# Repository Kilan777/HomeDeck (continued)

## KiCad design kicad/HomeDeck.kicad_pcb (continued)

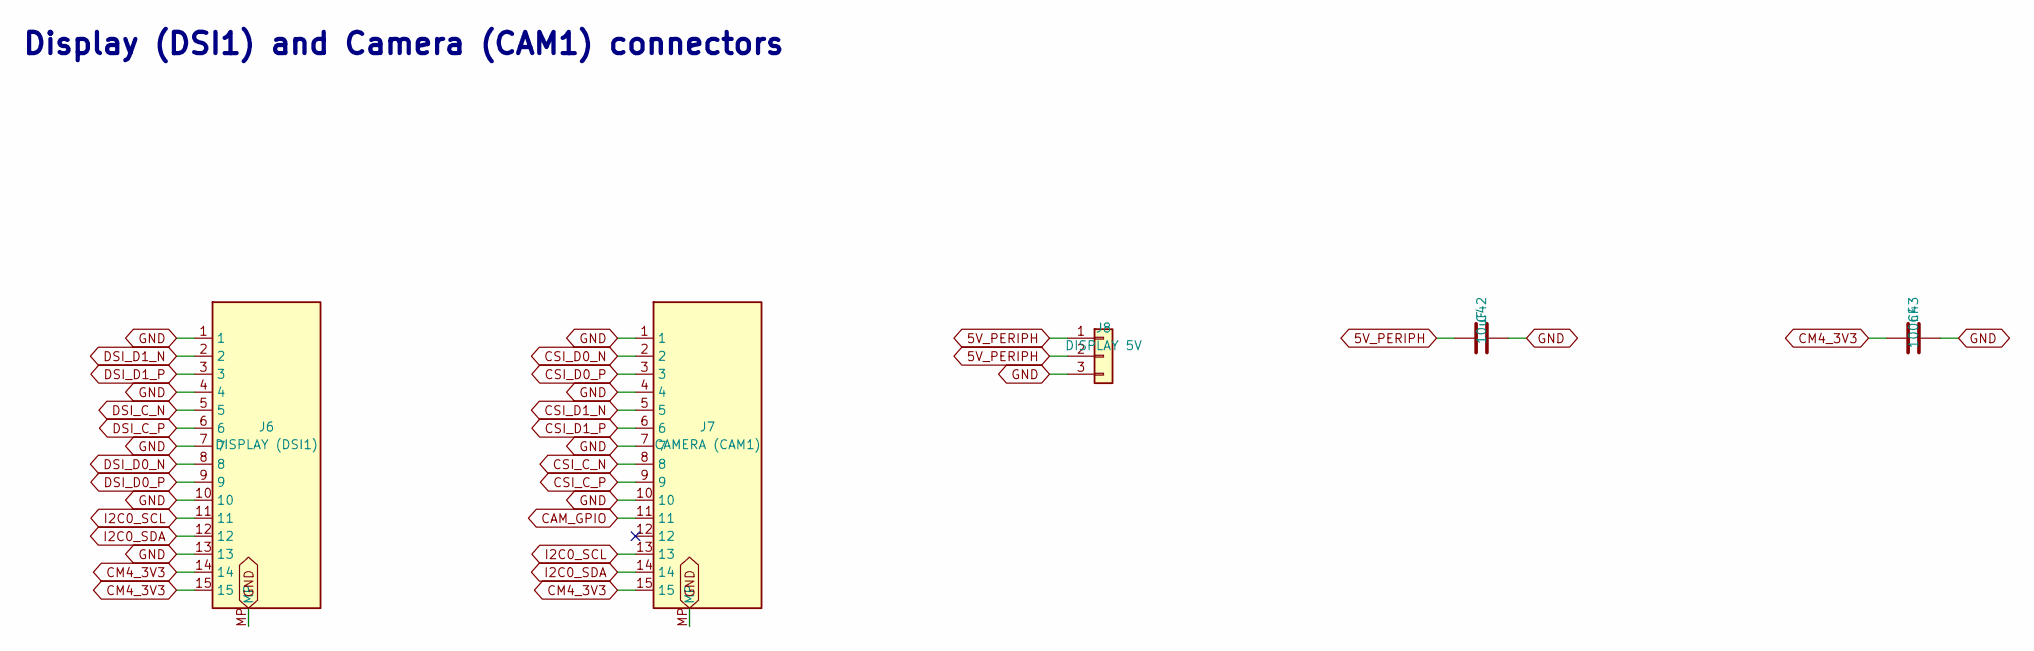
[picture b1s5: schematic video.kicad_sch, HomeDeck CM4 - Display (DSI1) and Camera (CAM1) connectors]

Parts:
C42: 10uF; C_0603_1608Metric; LCSC C96446
C43: 100nF; C_0603_1608Metric; LCSC C14663
J6: DISPLAY (DSI1); FPC_15P_1.0mm_BottomContact_RA; MPN 1.0-15PContact,Bottom; LCSC C66660
J7: CAMERA (CAM1); FPC_15P_1.0mm_BottomContact_RA; MPN 1.0-15PContact,Bottom; LCSC C66660
J8: DISPLAY 5V; PinHeader_1x03_P2.54mm_Vertical; MPN B-2100S03P-A110; LCSC C124376

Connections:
5V_PERIPH: C42.1, J8.1, J8.2; also elsewhere on the board
CAM_GPIO: J7.11; also elsewhere on the board
CM4_3V3: C43.1, J6.14, J6.15, J7.15; also elsewhere on the board
CSI_C_N: J7.8; also elsewhere on the board
CSI_C_P: J7.9; also elsewhere on the board
CSI_D0_N: J7.2; also elsewhere on the board
CSI_D0_P: J7.3; also elsewhere on the board
CSI_D1_N: J7.5; also elsewhere on the board
CSI_D1_P: J7.6; also elsewhere on the board
DSI_C_N: J6.5; also elsewhere on the board
DSI_C_P: J6.6; also elsewhere on the board
DSI_D0_N: J6.8; also elsewhere on the board
DSI_D0_P: J6.9; also elsewhere on the board
DSI_D1_N: J6.2; also elsewhere on the board
DSI_D1_P: J6.3; also elsewhere on the board
GND: C42.2, C43.2, J6.1, J6.4, J6.7, J6.10, J6.13, J6.MP, J7.1, J7.4, J7.7, J7.10, J7.MP, J8.3; also elsewhere on the board
I2C0_SCL: J6.11, J7.13; also elsewhere on the board
I2C0_SDA: J6.12, J7.14; also elsewhere on the board

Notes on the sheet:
Display (DSI1) and Camera (CAM1) connectors

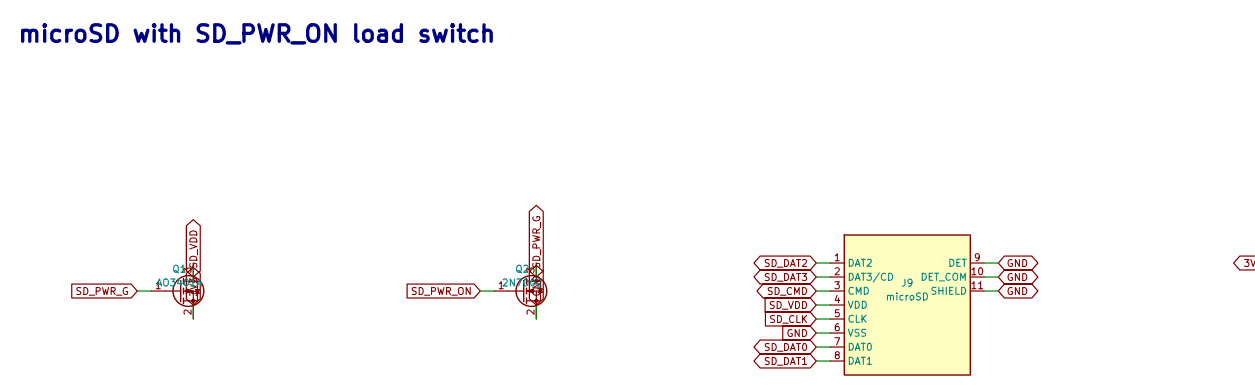
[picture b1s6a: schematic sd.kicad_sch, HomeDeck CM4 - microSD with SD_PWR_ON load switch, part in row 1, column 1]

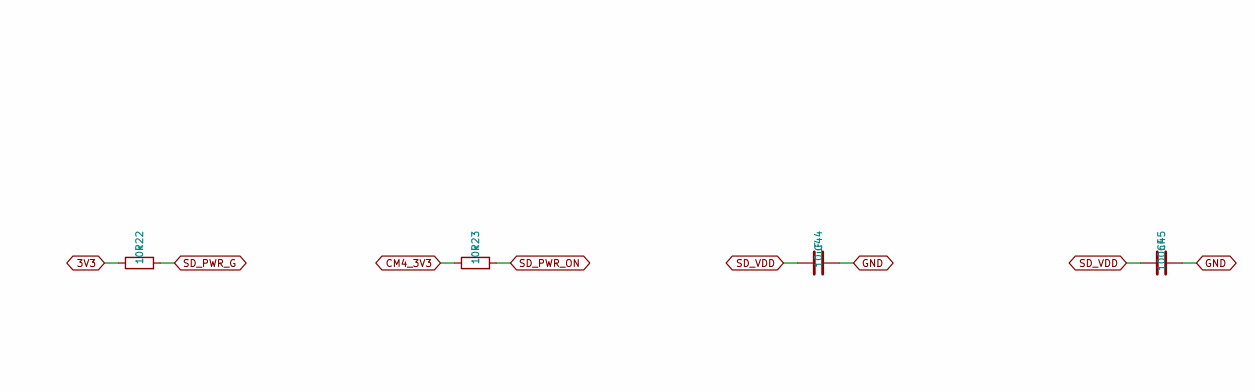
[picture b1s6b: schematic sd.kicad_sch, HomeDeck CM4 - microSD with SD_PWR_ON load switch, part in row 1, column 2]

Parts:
C44: 10uF; C_0603_1608Metric; LCSC C96446
C45: 100nF; C_0603_1608Metric; LCSC C14663
J9: microSD; microSD_HC_Molex_104031-0811; MPN 104031-0811; LCSC C585350
Q1: AO3401A; SOT-23; MPN AO3401A; LCSC C15127
Q2: 2N7002; SOT-23; MPN 2N7002; LCSC C8545
R22, R23: 10k; R_0603_1608Metric; LCSC C25804

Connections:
3V3: Q1.2 (S), R22.1; also elsewhere on the board
CM4_3V3: R23.1; also elsewhere on the board
GND: C44.2, C45.2, J9.6 (VSS), J9.9 (DET), J9.10 (DET_COM), J9.11 (SHIELD), Q2.2 (S); also elsewhere on the board
SD_CLK: J9.5 (CLK); also elsewhere on the board
SD_CMD: J9.3 (CMD); also elsewhere on the board
SD_DAT0: J9.7 (DAT0); also elsewhere on the board
SD_DAT1: J9.8 (DAT1); also elsewhere on the board
SD_DAT2: J9.1 (DAT2); also elsewhere on the board
SD_DAT3: J9.2 (DAT3/CD); also elsewhere on the board
SD_PWR_G: Q1.1 (G), Q2.3 (D), R22.2
SD_PWR_ON: Q2.1 (G), R23.2; also elsewhere on the board
SD_VDD: C44.1, C45.1, J9.4 (VDD), Q1.3 (D)

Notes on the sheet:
microSD with SD_PWR_ON load switch

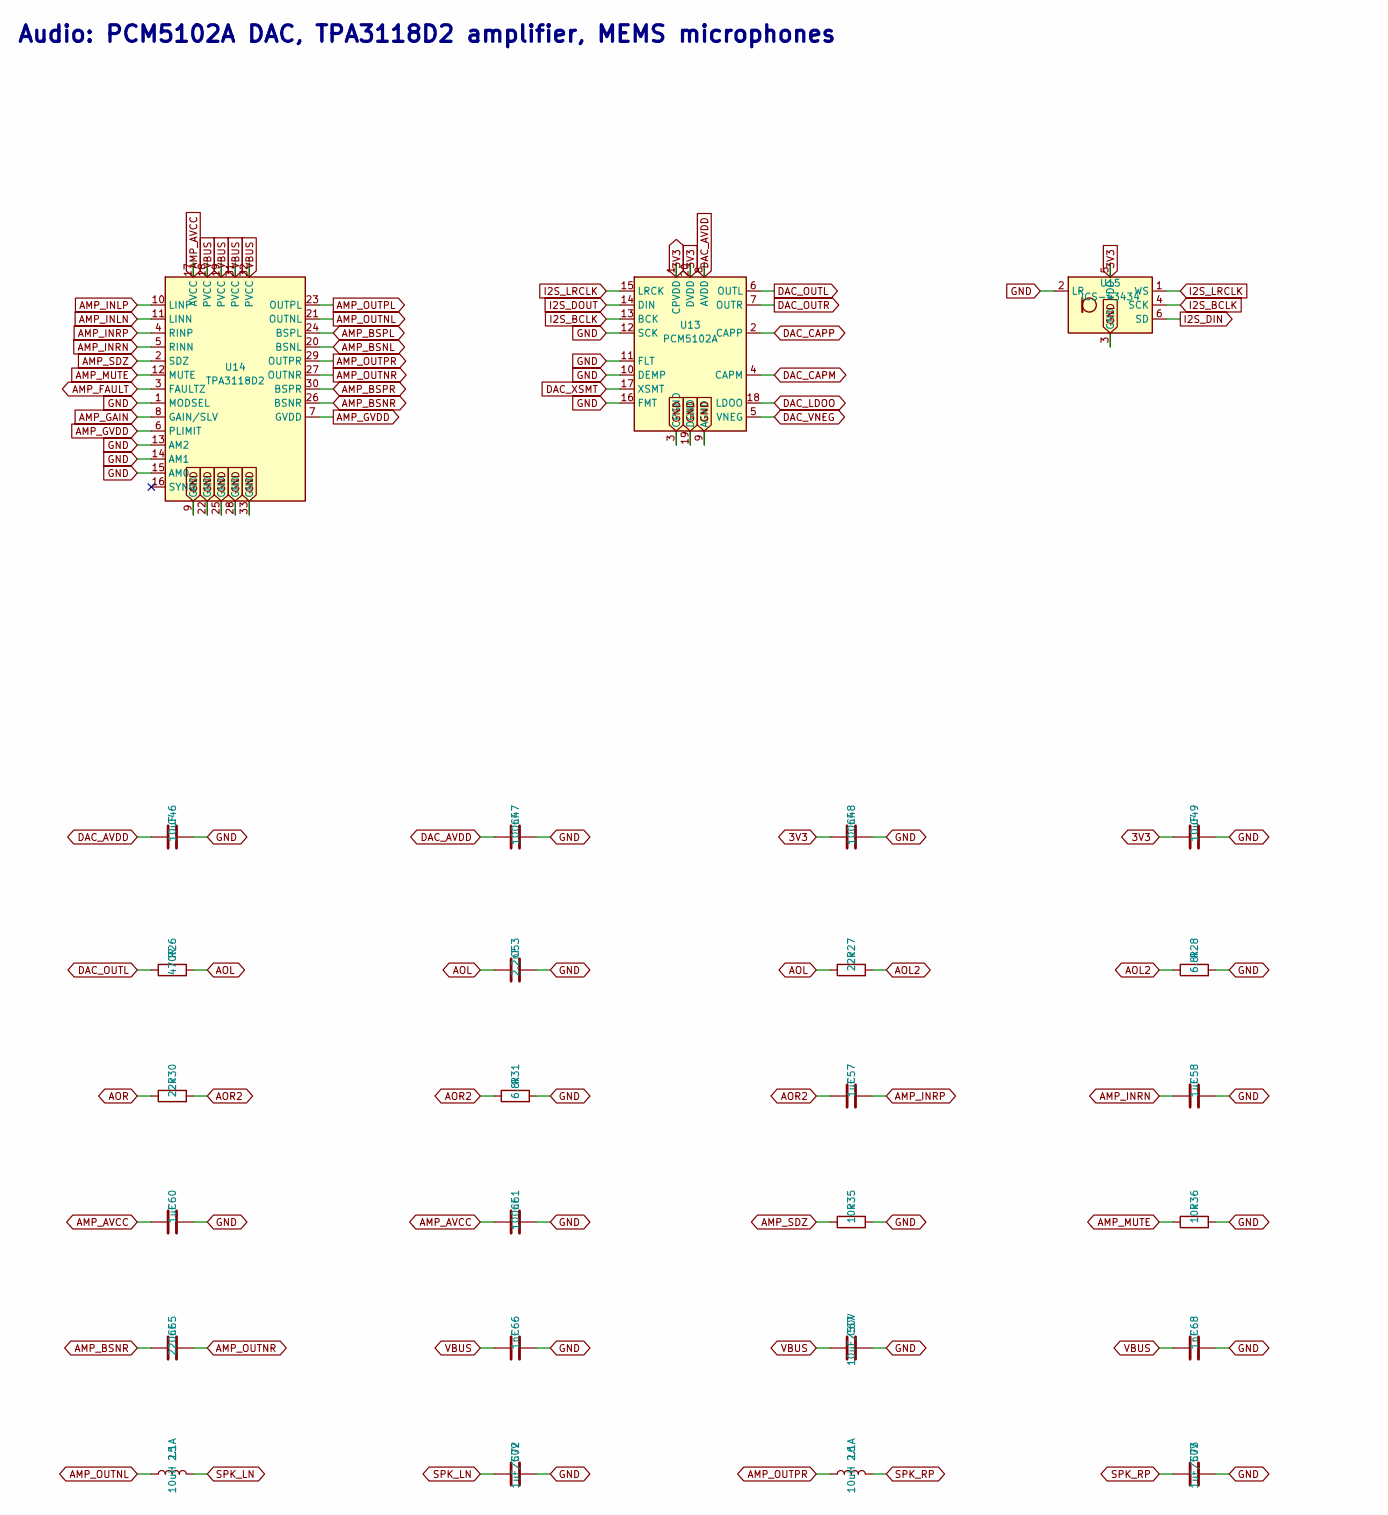
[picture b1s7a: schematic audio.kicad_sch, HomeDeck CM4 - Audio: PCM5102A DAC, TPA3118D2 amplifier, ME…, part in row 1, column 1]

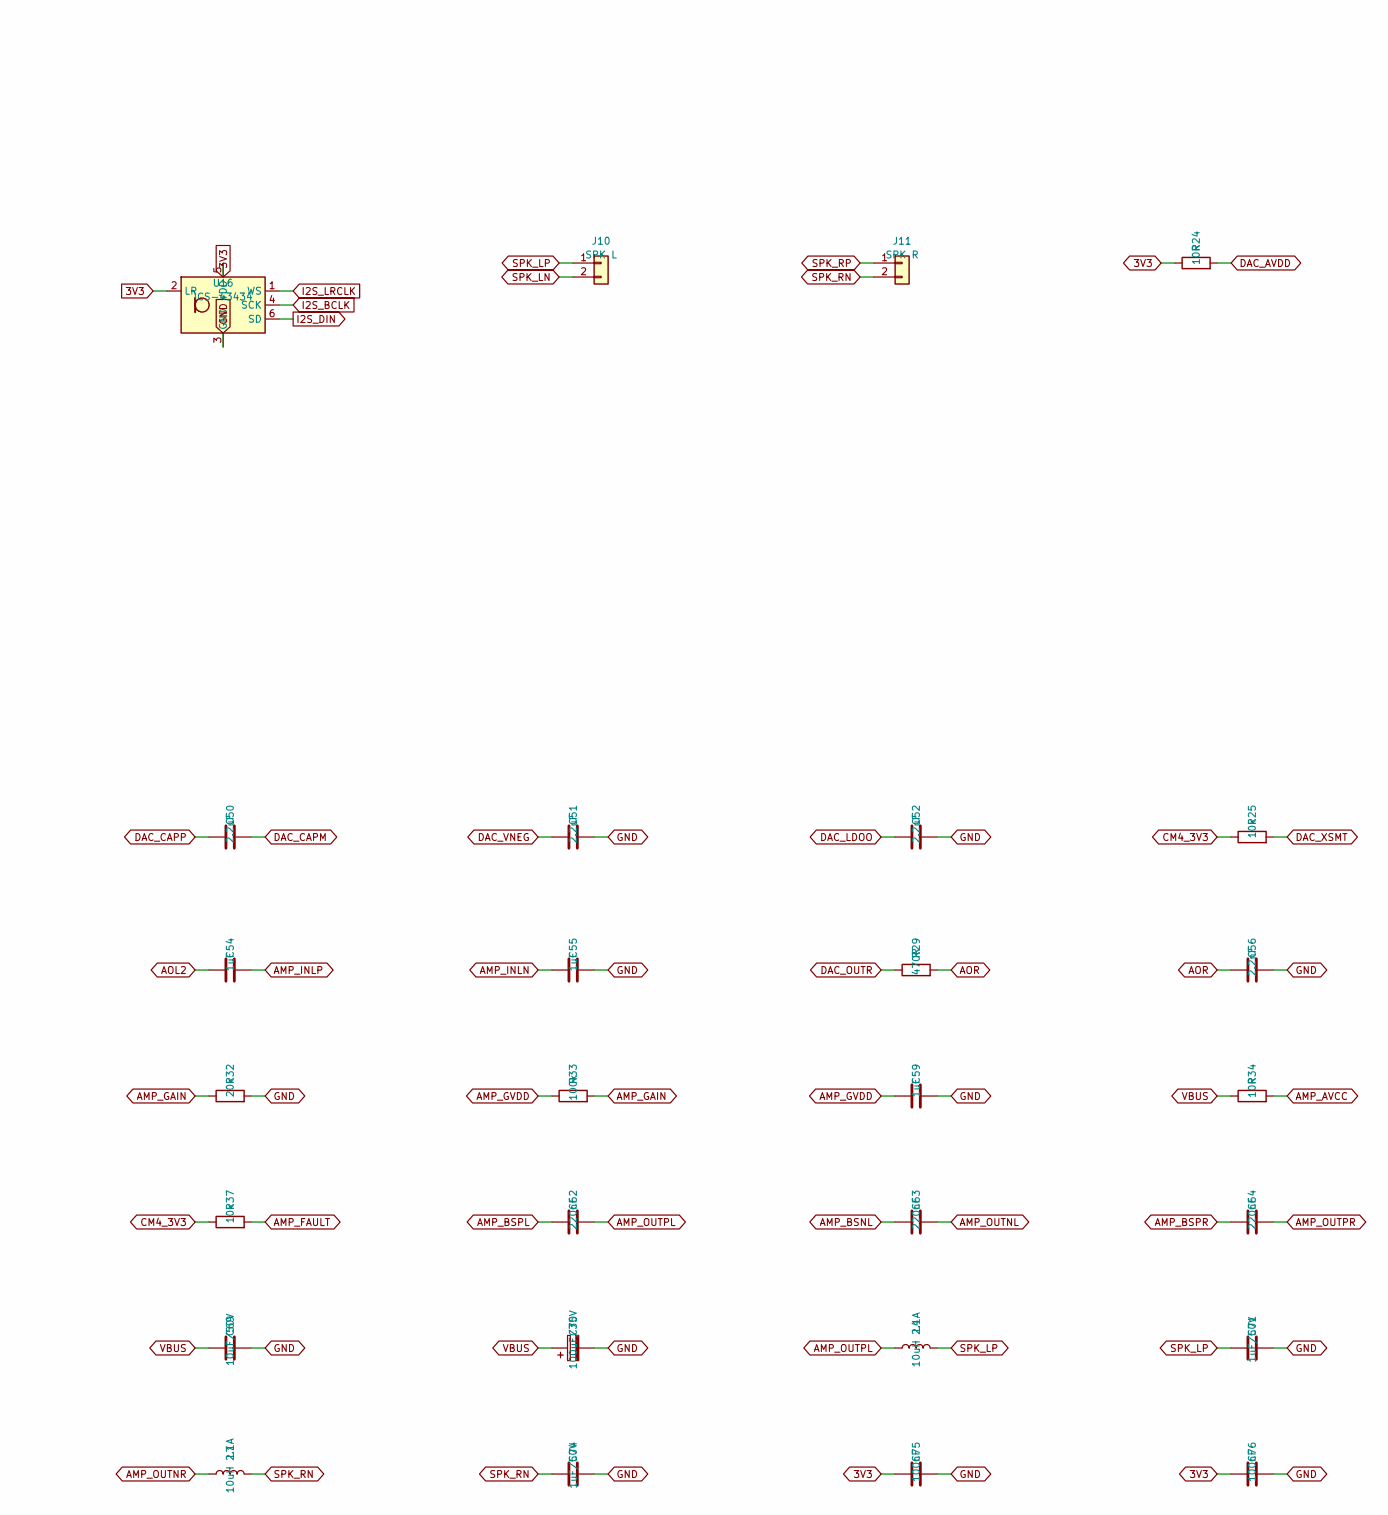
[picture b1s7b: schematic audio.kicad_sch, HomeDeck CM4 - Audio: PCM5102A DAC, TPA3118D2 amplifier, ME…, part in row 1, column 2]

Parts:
C46, C49: 10uF; C_0603_1608Metric; LCSC C96446
C47, C48, C61, C75, C76: 100nF; C_0603_1608Metric; LCSC C14663
C50, C51, C52: 2.2uF; C_0603_1608Metric; LCSC C23630
C53, C56: 2.2nF; C_0603_1608Metric; LCSC C1604
C54, C55, C57, C58, C59, C60: 1uF; C_0603_1608Metric; LCSC C15849
C62, C63, C64, C65: 220nF; C_0603_1608Metric; LCSC C21120
C66, C68: 1nF; C_0603_1608Metric; LCSC C1588
C67, C69: 10uF/50V; C_1206_3216Metric; LCSC C13585
C70: 100uF/35V; CP_Elec_6.3x7.7; LCSC C3339
C71, C72, C73, C74: 1uF/50V; C_0805_2012Metric; LCSC C28323
J10: SPK L; JST_PH_S2B-PH-K_1x02_P2.00mm_Horizontal; MPN S2B-PH-K-S; LCSC C173752
J11: SPK R; JST_PH_S2B-PH-K_1x02_P2.00mm_Horizontal; MPN S2B-PH-K-S; LCSC C173752
L4, L5, L6, L7: 10uH 2.1A; L_Sunlord_SWPA5040S; MPN SWPA5040S100MT; LCSC C84608
R24, R34: 10R; R_0603_1608Metric; LCSC C22859
R25, R35, R36, R37: 10k; R_0603_1608Metric; LCSC C25804
R26, R29: 470R; R_0603_1608Metric; LCSC C23179
R27, R30: 22k; R_0603_1608Metric; LCSC C31850
R28, R31: 6.8k; R_0603_1608Metric; LCSC C23212
R32: 20k; R_0603_1608Metric; LCSC C4184
R33: 100k; R_0603_1608Metric; LCSC C25803
U13: PCM5102A; TSSOP-20_4.4x6.5mm_P0.65mm; MPN PCM5102APWR; LCSC C107671
U14: TPA3118D2; HTSSOP-32-1EP_6.1x11mm_P0.65mm_EP5.2x11mm_Mask4.11x4.36mm_T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; MPN TPA3118D2DAPR; LCSC C46497
U15, U16: ICS-43434; InvenSense_ICS-43434-6_3.5x2.65mm; MPN ICS-43434; LCSC C5656610

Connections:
3V3: C48.1, C49.1, C75.1, C76.1, R24.1, U13.1 (CPVDD), U13.20 (DVDD), U15.5 (VDD), U16.2 (LR), U16.5 (VDD); also elsewhere on the board
AMP_AVCC: C60.1, C61.1, R34.2, U14.17 (AVCC)
AMP_BSNL: C63.1, U14.20 (BSNL)
AMP_BSNR: C65.1, U14.26 (BSNR)
AMP_BSPL: C62.1, U14.24 (BSPL)
AMP_BSPR: C64.1, U14.30 (BSPR)
AMP_FAULT: R37.2, U14.3 (FAULTZ); also elsewhere on the board
AMP_GAIN: R32.1, R33.2, U14.8 (GAIN/SLV)
AMP_GVDD: C59.1, R33.1, U14.6 (PLIMIT), U14.7 (GVDD)
AMP_INLN: C55.1, U14.11 (LINN)
AMP_INLP: C54.2, U14.10 (LINP)
AMP_INRN: C58.1, U14.5 (RINN)
AMP_INRP: C57.2, U14.4 (RINP)
AMP_MUTE: R36.1, U14.12 (MUTE); also elsewhere on the board
AMP_OUTNL: C63.2, L5.1, U14.21 (OUTNL)
AMP_OUTNR: C65.2, L7.1, U14.27 (OUTNR)
AMP_OUTPL: C62.2, L4.1, U14.23 (OUTPL)
AMP_OUTPR: C64.2, L6.1, U14.29 (OUTPR)
AMP_SDZ: R35.1, U14.2 (SDZ); also elsewhere on the board
AOL: C53.1, R26.2, R27.1
AOL2: C54.1, R27.2, R28.1
AOR: C56.1, R29.2, R30.1
AOR2: C57.1, R30.2, R31.1
CM4_3V3: R25.1, R37.1; also elsewhere on the board
DAC_AVDD: C46.1, C47.1, R24.2, U13.8 (AVDD)
DAC_CAPM: C50.2, U13.4 (CAPM)
DAC_CAPP: C50.1, U13.2 (CAPP)
DAC_LDOO: C52.1, U13.18 (LDOO)
DAC_OUTL: R26.1, U13.6 (OUTL)
DAC_OUTR: R29.1, U13.7 (OUTR)
DAC_VNEG: C51.1, U13.5 (VNEG)
DAC_XSMT: R25.2, U13.17 (XSMT); also elsewhere on the board
GND: C46.2, C47.2, C48.2, C49.2, C51.2, C52.2, C53.2, C55.2, C56.2, C58.2, C59.2, C60.2, C61.2, C66.2, C67.2, C68.2, C69.2, C70.2, C71.2, C72.2, C73.2, C74.2, C75.2, C76.2, R28.2, R31.2, R32.2, R35.2, R36.2, U13.3 (CPGND), U13.9 (AGND), U13.10 (DEMP), U13.11 (FLT), U13.12 (SCK), U13.16 (FMT), U13.19 (DGND), U14.1 (MODSEL), U14.9 (GND), U14.13 (AM2), U14.14 (AM1), U14.15 (AM0), U14.22 (GND), U14.25 (GND), U14.28 (GND), U14.33 (GND), U15.2 (LR), U15.3 (GND), U16.3 (GND); also elsewhere on the board
I2S_BCLK: U13.13 (BCK), U15.4 (SCK), U16.4 (SCK); also elsewhere on the board
I2S_DIN: U15.6 (SD), U16.6 (SD); also elsewhere on the board
I2S_DOUT: U13.14 (DIN); also elsewhere on the board
I2S_LRCLK: U13.15 (LRCK), U15.1 (WS), U16.1 (WS); also elsewhere on the board
SPK_LN: C72.1, J10.2, L5.2
SPK_LP: C71.1, J10.1, L4.2
SPK_RN: C74.1, J11.2, L7.2
SPK_RP: C73.1, J11.1, L6.2
VBUS: C66.1, C67.1, C68.1, C69.1, C70.1, R34.1, U14.18 (PVCC), U14.19 (PVCC), U14.31 (PVCC), U14.32 (PVCC); also elsewhere on the board

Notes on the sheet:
Audio: PCM5102A DAC, TPA3118D2 amplifier, MEMS microphones

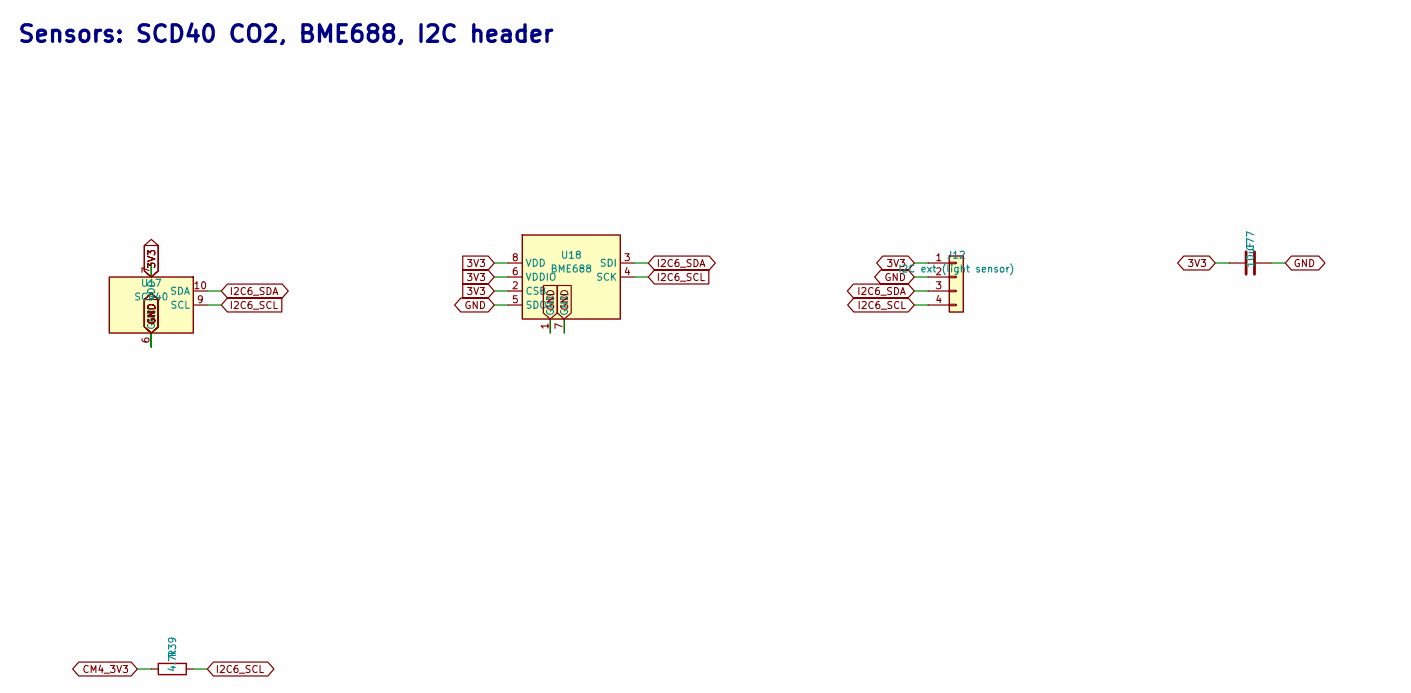
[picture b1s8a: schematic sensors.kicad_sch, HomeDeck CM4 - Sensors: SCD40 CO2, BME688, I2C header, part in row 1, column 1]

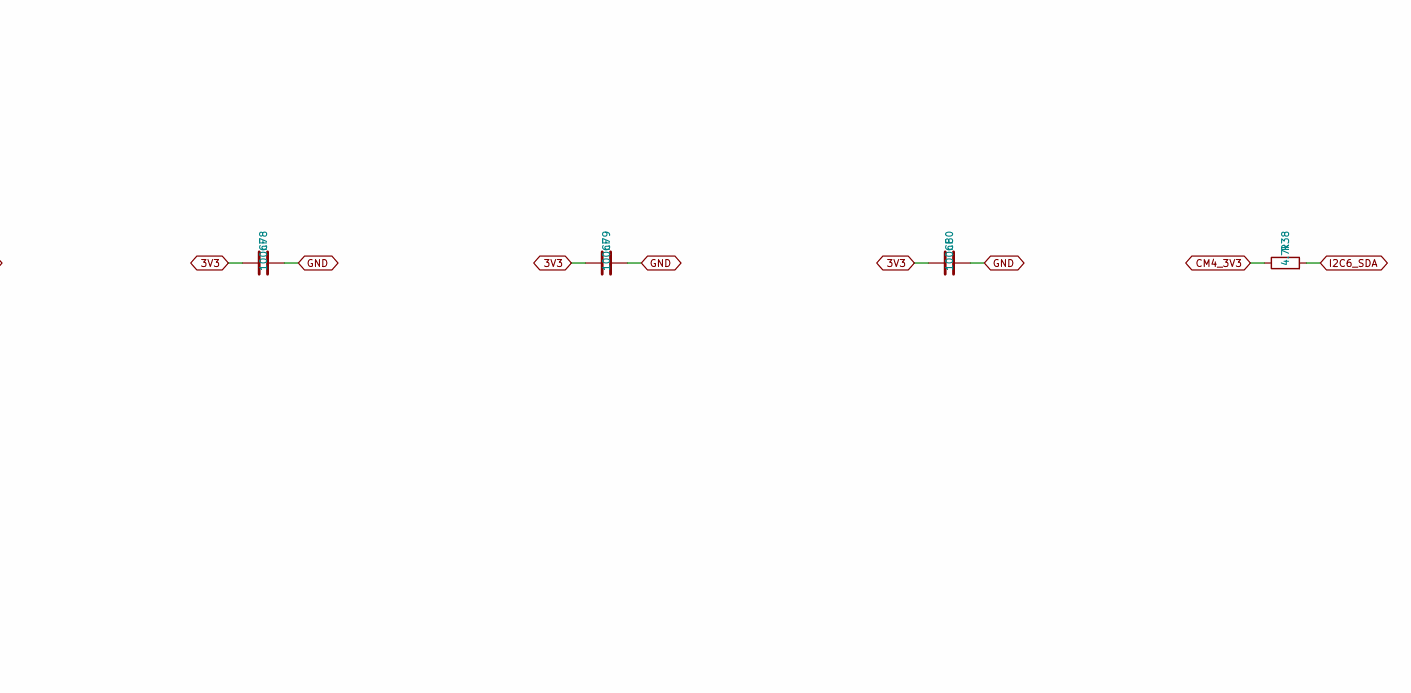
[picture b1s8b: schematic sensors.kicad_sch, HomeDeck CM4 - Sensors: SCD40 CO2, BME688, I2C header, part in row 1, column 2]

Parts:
C77: 10uF; C_0603_1608Metric; LCSC C96446
C78, C79, C80: 100nF; C_0603_1608Metric; LCSC C14663
J12: I2C ext (light sensor); PinHeader_1x04_P2.54mm_Vertical; MPN B-2100S04P-A110; LCSC C124378
R38, R39: 4.7k; R_0603_1608Metric; LCSC C23162
U17: SCD40; Sensirion_SCD4x-1EP_10.1x10.1mm_P1.25mm_EP4.8x4.8mm; MPN SCD40-D-R2; LCSC C3659421
U18: BME688; Bosch_LGA-8_3x3mm_P0.8mm_ClockwisePinNumbering; MPN BME688; LCSC C3664478

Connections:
3V3: C77.1, C78.1, C79.1, C80.1, J12.1, U17.7 (VDD), U17.19 (VDD), U18.2 (CSB), U18.6 (VDDIO), U18.8 (VDD); also elsewhere on the board
CM4_3V3: R38.1, R39.1; also elsewhere on the board
GND: C77.2, C78.2, C79.2, C80.2, J12.2, U17.6 (GND), U17.20 (GND), U17.21 (GND), U18.1 (GND), U18.5 (SDO), U18.7 (GND); also elsewhere on the board
I2C6_SCL: J12.4, R39.2, U17.9 (SCL), U18.4 (SCK); also elsewhere on the board
I2C6_SDA: J12.3, R38.2, U17.10 (SDA), U18.3 (SDI); also elsewhere on the board

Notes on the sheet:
Sensors: SCD40 CO2, BME688, I2C header

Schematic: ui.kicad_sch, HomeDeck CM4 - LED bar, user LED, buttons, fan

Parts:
C81, C82, C83, C84, C85, C86, C87, C88, C89, C90, C91, C93, C94, C95: 100nF; C_0603_1608Metric; LCSC C14663
C92: 10uF; C_0603_1608Metric; LCSC C96446
D5: USER (green); LED_0805_2012Metric; MPN KT-0805G; LCSC C2297
D6: SS34; D_SMA; MPN SS34; LCSC C8678
D10, D11, D12, D13, D14, D15, D16, D17, D18, D19: WS2812B; LED_WS2812B_PLCC4_5.0x5.0mm_P3.2mm; MPN WS2812B-B/T; LCSC C2761795
J17: LED strip ext; JST_PH_S3B-PH-K_1x03_P2.00mm_Horizontal; MPN S3B-PH-K-S; LCSC C157929
J18, J19, J20: ext button; PinHeader_1x02_P2.54mm_Vertical; MPN B-2100S02P-A110; LCSC C124375
J21: FAN 5V; JST_PH_S2B-PH-K_1x02_P2.00mm_Horizontal; MPN S2B-PH-K-S; LCSC C173752
Q3: AO3400A; SOT-23; MPN AO3400A; LCSC C20917
R40: 330R; R_0603_1608Metric; LCSC C23138
R41: 470R; R_0603_1608Metric; LCSC C23179
R42, R43, R44: 10k; R_0603_1608Metric; LCSC C25804
R45: 100R; R_0603_1608Metric; LCSC C22775
R46: 100k; R_0603_1608Metric; LCSC C25803
SW1: POWER; SW_Push_1P1T_XKB_TS-1187A; MPN TS-1187A-B-A-B; LCSC C318884
SW2: BTN A; SW_Push_1P1T_XKB_TS-1187A; MPN TS-1187A-B-A-B; LCSC C318884
SW3: BTN B; SW_Push_1P1T_XKB_TS-1187A; MPN TS-1187A-B-A-B; LCSC C318884
U19: 74AHCT1G125; SOT-23-5; MPN SN74AHCT1G125DBVR; LCSC C7484

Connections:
5V_PERIPH: C81.1, C82.1, C83.1, C84.1, C85.1, C86.1, C87.1, C88.1, C89.1, C90.1, C91.1, C92.1, D6.1 (K), D10.1 (VDD), D11.1 (VDD), D12.1 (VDD), D13.1 (VDD), D14.1 (VDD), D15.1 (VDD), D16.1 (VDD), D17.1 (VDD), D18.1 (VDD), D19.1 (VDD), J17.1, J21.1, U19.5 (VCC); also elsewhere on the board
BTN_A: C94.1, J19.1, R43.2, SW2.1; also elsewhere on the board
BTN_B: C95.1, J20.1, R44.2, SW3.1; also elsewhere on the board
CM4_3V3: R42.1, R43.1, R44.1; also elsewhere on the board
FAN_G: Q3.1 (G), R45.2, R46.1
FAN_N: D6.2 (A), J21.2, Q3.3 (D)
FAN_PWM: R45.1; also elsewhere on the board
GND: C81.2, C82.2, C83.2, C84.2, C85.2, C86.2, C87.2, C88.2, C89.2, C90.2, C91.2, C92.2, C93.2, C94.2, C95.2, D5.1 (K), D10.3 (VSS), D11.3 (VSS), D12.3 (VSS), D13.3 (VSS), D14.3 (VSS), D15.3 (VSS), D16.3 (VSS), D17.3 (VSS), D18.3 (VSS), D19.3 (VSS), J17.3, J18.2, J19.2, J20.2, Q3.2 (S), R46.2, SW1.2, SW2.2, SW3.2, U19.1, U19.3 (GND); also elsewhere on the board
LED_D0: D10.4 (DIN), R40.2
LED_D1: D10.2 (DOUT), D11.4 (DIN)
LED_D2: D11.2 (DOUT), D12.4 (DIN)
LED_D3: D12.2 (DOUT), D13.4 (DIN)
LED_D4: D13.2 (DOUT), D14.4 (DIN)
LED_D5: D14.2 (DOUT), D15.4 (DIN)
LED_D6: D15.2 (DOUT), D16.4 (DIN)
LED_D7: D16.2 (DOUT), D17.4 (DIN)
LED_D8: D17.2 (DOUT), D18.4 (DIN)
LED_D9: D18.2 (DOUT), D19.4 (DIN)
LED_D10: D19.2 (DOUT), J17.2
LED_DATA: U19.2; also elsewhere on the board
LED_DATA_5V: R40.1, U19.4
PWR_BTN: C93.1, J18.1, R42.2, SW1.1; also elsewhere on the board
USER_LED: R41.1; also elsewhere on the board
USER_LED_A: D5.2 (A), R41.2

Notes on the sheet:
LED bar, user LED, buttons, fan

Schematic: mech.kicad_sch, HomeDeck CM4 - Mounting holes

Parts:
H1, H2, H3, H4: M2.5 display standoff; MountingHole_2.7mm_M2.5

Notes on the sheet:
Mounting holes

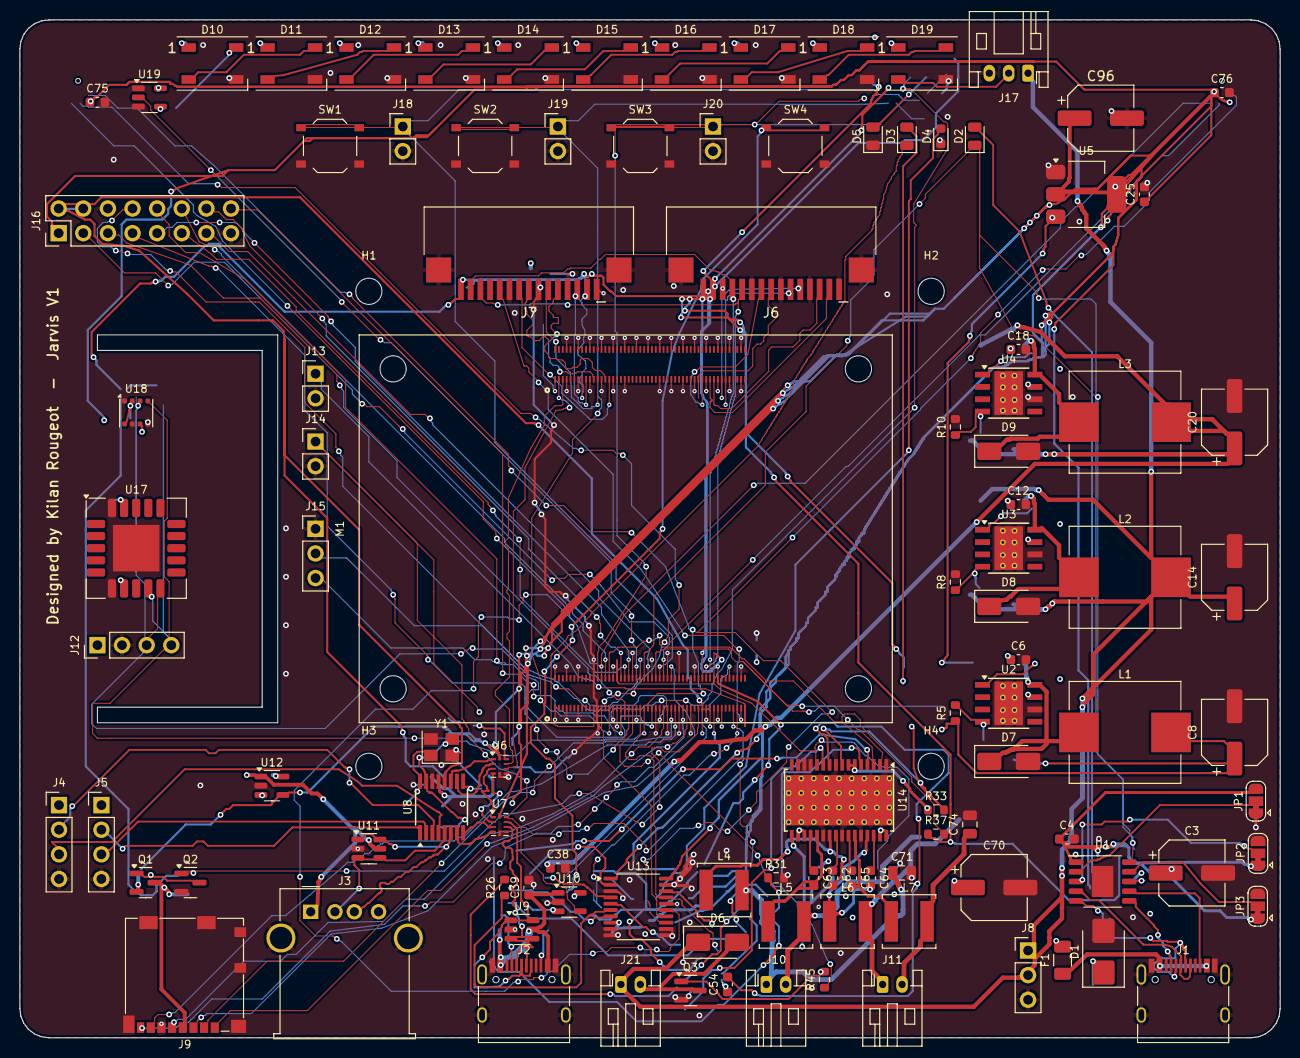
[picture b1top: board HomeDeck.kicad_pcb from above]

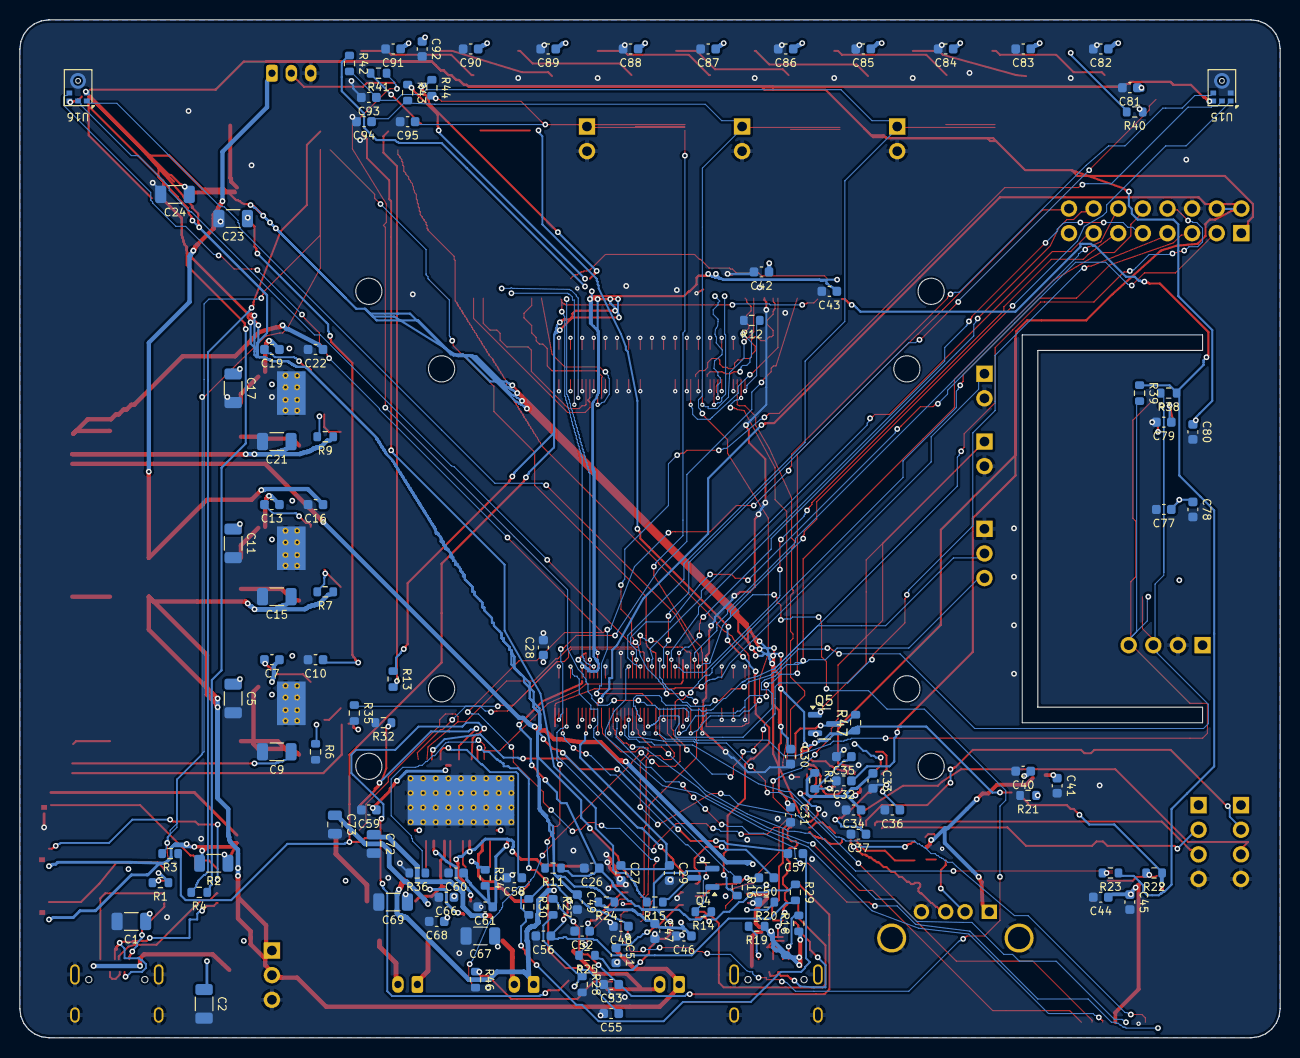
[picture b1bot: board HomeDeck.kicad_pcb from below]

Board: 4 copper layers, 130.0 x 105.0 mm, 228 parts (117 on the bottom side), 161 nets.

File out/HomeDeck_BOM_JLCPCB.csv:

Comment,Designator,Footprint,LCSC Part #,MPN,JLC type,Description,JLC stock (2026-09-06)
TYPE-C-31-M-12,"J1,J2",USB_C_Receptacle_HRO_TYPE-C-31-M-12,C165948,TYPE-C-31-M-12,Extended,USB-C receptacle 16P (power input),295816
5A,F1,Fuse_1206_3216Metric,C48332,SF-1206F500-2,Extended,5 A fast-acting 1206 fuse (Bourns),10183
SMBJ24A,D1,D_SMB,C87268,SMBJ24A,Extended,"VBUS TVS, cathode (band) to VBUS",31850
10uF/50V,"C1,C2,C5,C11,C17,C67,C69",C_1206_3216Metric,C13585,,Basic,,3886433
100uF/35V,"C3,C8,C14,C20,C96,C70",CP_Elec_6.3x7.7,C3339,,Extended,,45052
CH224K,U1,ESSOP-10-1EP_3.9x4.9mm_P1.0mm,C970725,CH224K,Extended,USB PD sink controller,3137
5.1k,"R1,R21",R_0603_1608Metric,C23186,,Basic,,24366811
1k/0.25W,R2,R_1206_3216Metric,C4410,,Basic,,3103095
1uF,"C4,C32,C54,C55,C57,C58,C59,C60",C_0603_1608Metric,C15849,,Basic,,9141046
10k,"R3,R11,R47,R17,R22,R23,R25,R35,R36,R37,R42,R43,R44",R_0603_1608Metric,C25804,,Basic,,32438109
KT-0805G,"D2,D3,D5",LED_0805_2012Metric,C2297,KT-0805G,Basic,,1844100
470R,"R4,R26,R29,R41",R_0603_1608Metric,C23179,,Basic,,7850550
TPS5430,"U2,U3,U4",TI_SO-PowerPAD-8_ThermalVias,C9864,TPS5430DDAR,Basic,3A buck -> 5V_SYS,149924
100nF,"C6,C10,C12,C16,C18,C22,C25,C26,C29,C30,C31,C34,C35,C43,C45,C47,C48,C61,C75,C76,C78,C79,C80,C81,C82,C83,C84,C85,C86,C87,C88,C89,C90,C91,C93,C94,C95",C_0603_1608Metric,C14663,,Basic,,65400153
10nF,"C7,C13,C19",C_0603_1608Metric,C57112,,Basic,,9208836
SS34,"D7,D8,D9,D6",D_SMA,C8678,SS34,Basic,,5300408
10uH 7.8A,"L1,L2,L3",L_Sunlord_MWSA1004S,C408487,MWSA1004S-100MT,Extended,,8080
22uF/25V,"C9,C15,C21,C23,C24",C_1206_3216Metric,C12891,,Basic,,1473417
15k,"R5,R7,R9",R_0603_1608Metric,C22809,,Basic,,5368460
4.7k,"R6,R8,R10,R38,R39",R_0603_1608Metric,C23162,,Basic,,28145041
AMS1117-3.3,U5,SOT-223-3_TabPin2,C6186,AMS1117-3.3,Basic,,1493311
10uF,"C27,C28,C33,C38,C39,C40,C41,C42,C44,C46,C49,C77,C92",C_0603_1608Metric,C96446,,Basic,,4908933
330R,"R13,R40",R_0603_1608Metric,C23138,,Basic,,4491301
AO3401A,"Q4,Q1",SOT-23,C15127,AO3401A,Basic,PWR LED buffer,715738
100k,"R14,R33,R46",R_0603_1608Metric,C25803,,Basic,,25165711
PWR (red),D4,LED_0603_1608Metric,C2286,KT-0603R,Basic,,4584108
1k,R15,R_0603_1608Metric,C21190,,Basic,,29352441
B-2100S02P-A110,"J13,J14,J18,J19,J20",PinHeader_1x02_P2.54mm_Vertical,C124375,B-2100S02P-A110,Extended,,182578
B-2100S03P-A110,"J15,J8",PinHeader_1x03_P2.54mm_Vertical,C124376,B-2100S03P-A110,Extended,,18108
Expansion,J16,PinHeader_2x08_P2.54mm_Vertical,C492425,PZ254V-12-16P,Extended,,29777
TS-1187A-B-A-B,"SW4,SW1,SW2,SW3",SW_Push_1P1T_XKB_TS-1187A,C318884,TS-1187A-B-A-B,Basic,,860979
220R,R16,R_0603_1608Metric,C22962,,Basic,,2214404
TS3USB221,"U6,U7",Texas_UQFN-10_1.5x2mm_P0.5mm,C130085,TS3USB221RSER,Extended,USB 2.0 2:1 mux,36241
2N7002,"Q5,Q2",SOT-23,C8545,2N7002,Basic,nRPIBOOT inverter for U6 select,2245681
CH334R,U8,QSOP-16_3.9x4.9mm_P0.635mm,C4154405,CH334R,Extended,USB 2.0 4-port hub,26952
12MHz,Y1,Crystal_SMD_3225-4Pin_3.2x2.5mm,C9002,X322512MSB4SI,Basic,,142602
22k,"R18,R19,R27,R30",R_0603_1608Metric,C31850,,Basic,,4382672
USBLC6-2SC6,"U9,U11",SOT-23-6,C7519,USBLC6-2SC6,Extended,,48108
SY6280AAC,"U10,U12",SOT-23-5,C55136,SY6280AAC,Extended,USB-C #2 power switch 1.3A,32462
3.9k,R20,R_0603_1608Metric,C23018,,Basic,,1171777
USB-A,J3,USB_A_Molex_67643_Horizontal,C2346,901-211A1021D10100,Extended,,33420
B-2100S04P-A110,"J4,J5,J12",PinHeader_1x04_P2.54mm_Vertical,C124378,B-2100S04P-A110,Extended,,105951
"1.0-15PContact,Bottom","J6,J7",FPC_15P_1.0mm_BottomContact_RA,C66660,"1.0-15PContact,Bottom",Extended,"15-pin 1.0mm FPC, bottom contact, right angle (BOOMELE)",3138
microSD,J9,microSD_HC_Molex_104031-0811,C585350,104031-0811,Extended,,13273
PCM5102A,U13,TSSOP-20_4.4x6.5mm_P0.65mm,C107671,PCM5102APWR,Extended,I2S stereo DAC,10504
10R,"R24,R34",R_0603_1608Metric,C22859,,Basic,,9636923
2.2uF,"C50,C51,C52",C_0603_1608Metric,C23630,,Basic,,3821265
2.2nF,"C53,C56",C_0603_1608Metric,C1604,,Basic,,1417575
6.8k,"R28,R31",R_0603_1608Metric,C23212,,Basic,,2243339
TPA3118D2,U14,HTSSOP-32-1EP_6.1x11mm_P0.65mm_EP5.2x11mm_Mask4.11x4.36mm_ThermalVias,C46497,TPA3118D2DAPR,Extended,Stereo class-D amplifier,39991
20k,R32,R_0603_1608Metric,C4184,,Basic,,7878441
220nF,"C62,C63,C64,C65",C_0603_1608Metric,C21120,,Basic,,1068539
1nF,"C66,C68",C_0603_1608Metric,C1588,,Basic,,10301799
10uH 2.1A,"L4,L5,L6,L7",L_Sunlord_SWPA5040S,C84608,SWPA5040S100MT,Extended,,72976
1uF/50V,"C71,C72,C73,C74",C_0805_2012Metric,C28323,,Basic,,3981237
S2B-PH-K-S,"J10,J11,J21",JST_PH_S2B-PH-K_1x02_P2.00mm_Horizontal,C173752,S2B-PH-K-S,Extended,,29753
ICS-43434,"U15,U16",InvenSense_ICS-43434-6_3.5x2.65mm,C5656610,ICS-43434,Extended,I2S MEMS mic LEFT,4500
SCD40,U17,Sensirion_SCD4x-1EP_10.1x10.1mm_P1.25mm_EP4.8x4.8mm,C3659421,SCD40-D-R2,Extended,CO2 sensor,3075
BME688,U18,Bosch_LGA-8_3x3mm_P0.8mm_ClockwisePinNumbering,C3664478,BME688,Extended,Temp/humidity/pressure/VOC,1339
74AHCT1G125,U19,SOT-23-5,C7484,SN74AHCT1G125DBVR,Extended,3.3->5V level shifter,26202
WS2812B,"D10,D11,D12,D13,D14,D15,D16,D17,D18,D19",LED_WS2812B_PLCC4_5.0x5.0mm_P3.2mm,C2761795,WS2812B-B/T,Extended,,167528
LED strip ext,J17,JST_PH_S3B-PH-K_1x03_P2.00mm_Horizontal,C157929,S3B-PH-K-S,Extended,,155016
AO3400A,Q3,SOT-23,C20917,AO3400A,Basic,,964371
100R,R45,R_0603_1608Metric,C22775,,Basic,,13946107
DF40C-100DS-0.4V(51),"M1A,M1B",Hirose_DF40C-100DS-0.4V,C597931,DF40C-100DS-0.4V(51),Extended,"CM4 socket, 100-pin 0.4 mm, 1.5 mm stack (genuine Hirose; low stock, may be pre-order)",25

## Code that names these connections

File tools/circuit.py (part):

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    c.R("1k/0.25W", "VBUS", "PD_VDD", "C4410", sh, size="1206")  # CH224K VDD is an internal shunt regulator fed through 1k from VBUS
    c.C("1uF", "PD_VDD", "GND", L["C1u"], sh)
    # voltage select solder jumpers: default CFG1=0, CFG2=1, CFG3=1 -> 15 V
    for name, net, pin1, pin3 in (("JP1", "PD_CFG1", "GND", "PD_VDD"), ("JP2", "PD_CFG2", "PD_VDD", "GND"), ("JP3", "PD_CFG3", "PD_VDD", "GND")):
        jp = c.add("JP", "Jumper", "SolderJumper_3_Bridged12", "PD volt sel", "Jumper:SolderJumper-3_P1.3mm_Bridged12_RoundedPad1.0x1.5mm", "", sh, ref=name)
        jp.cn({1: pin1, 2: net, 3: pin3})
    c.R("10k", "CM4_3V3", "PD_GOOD", L["R10k"], sh)
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    # ------------------------------------------------------------ CM4
    sh = "cm4"
    m = c.add("M", "HomeDeck", "RPi_CM4", "Raspberry Pi CM4", None, "", sh, mpn="CM4", ref="M1", desc="Compute Module 4 (2x DF40C-100DS-0.4V(51), JLC C597931)")
    gpio_nets = {2: "GPIO2", 3: "PWR_BTN", 4: "AMP_SDZ", 5: "AMP_MUTE", 6: "AMP_FAULT", 7: "GPIO7", 8: "GPIO8", 9: "GPIO9",
                 10: "LED_DATA", 11: "GPIO11", 12: "USER_LED", 13: "GPIO13", 14: "UART_TX", 15: "UART_RX", 16: "BTN_A", 17: "GPIO17",
                 18: "I2S_BCLK", 19: "I2S_LRCLK", 20: "I2S_DIN", 21: "I2S_DOUT", 22: "I2C6_SDA", 23: "I2C6_SCL", 24: "DAC_XSMT",
                 25: "FAN_PWM", 26: "BTN_B", 27: "PD_GOOD"}
    m.c(**{f"GPIO{k}": v for k, v in gpio_nets.items()})
    m.c(ID_SD="ID_SD", ID_SC="ID_SC")
    m.cn({77: "5V_SYS", 79: "5V_SYS", 81: "5V_SYS", 83: "5V_SYS", 85: "5V_SYS", 87: "5V_SYS"})
    m.c(GPIO_VREF="CM4_3V3")
    m.cn({84: "CM4_3V3", 86: "CM4_3V3"})
    m.c(GND="GND", GLOBAL_EN="GLOBAL_EN", RUN_PG="RUN_PG", nRPIBOOT="nRPIBOOT", Pi_nLED_Activity="ACT_LED_K", PI_LED_nPWR="PWR_LED_K",
        Camera_GPIO="CAM_GPIO", SCL0="I2C0_SCL", SDA0="I2C0_SDA", SD_PWR_ON="SD_PWR_ON", USB_P="USB_CM4_P", USB_N="USB_CM4_N", USB_OTG_ID="USB_OTG_ID",
        SD_CLK="SD_CLK", SD_CMD="SD_CMD", SD_DAT0="SD_DAT0", SD_DAT1="SD_DAT1", SD_DAT2="SD_DAT2", SD_DAT3="SD_DAT3",
        DSI1_D0_N="DSI_D0_N", DSI1_D0_P="DSI_D0_P", DSI1_D1_N="DSI_D1_N", DSI1_D1_P="DSI_D1_P", DSI1_C_N="DSI_C_N", DSI1_C_P="DSI_C_P",
        CAM1_D0_N="CSI_D0_N", CAM1_D0_P="CSI_D0_P", CAM1_D1_N="CSI_D1_N", CAM1_D1_P="CSI_D1_P", CAM1_C_N="CSI_C_N", CAM1_C_P="CSI_C_P")
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    led.cn({1: "GND", 2: "PWR_LED_A"})
    c.R("1k", "PWR_LED_D", "PWR_LED_A", L["R1k"], sh)
    # headers: GLOBAL_EN, nRPIBOOT jumper, UART, expansion
    jj = c.add("J", "Connector_Generic", "Conn_01x02", "GLOBAL_EN", "Connector_PinHeader_2.54mm:PinHeader_1x02_P2.54mm_Vertical", "C124375", sh, mpn="B-2100S02P-A110", ref="J13")
    jj.cn({1: "GLOBAL_EN", 2: "GND"})
    jj = c.add("J", "Connector_Generic", "Conn_01x02", "nRPIBOOT", "Connector_PinHeader_2.54mm:PinHeader_1x02_P2.54mm_Vertical", "C124375", sh, mpn="B-2100S02P-A110", ref="J14")
    jj.cn({1: "nRPIBOOT", 2: "GND"})
    jj = c.add("J", "Connector_Generic", "Conn_01x03", "UART debug", "Connector_PinHeader_2.54mm:PinHeader_1x03_P2.54mm_Vertical", "C124376", sh, mpn="B-2100S03P-A110", ref="J15")
    jj.cn({1: "GND", 2: "UART_TX", 3: "UART_RX"})
    jj = c.add("J", "Connector_Generic", "Conn_02x08_Odd_Even", "Expansion", "Connector_PinHeader_2.54mm:PinHeader_2x08_P2.54mm_Vertical", "C492425", sh, mpn="PZ254V-12-16P", ref="J16")
    jj.cn({1: "3V3", 2: "5V_SYS", 3: "GPIO2", 4: "5V_SYS", 5: "GPIO7", 6: "GND", 7: "GPIO8", 8: "UART_TX", 9: "GPIO9", 10: "UART_RX",
           11: "GPIO11", 12: "GPIO13", 13: "GPIO17", 14: "ID_SD", 15: "GND", 16: "ID_SC"})
    sw = c.add("SW", "Switch", "SW_Push", "RESET", "Button_Switch_SMD:SW_Push_1P1T_XKB_TS-1187A", "C318884", sh, mpn="TS-1187A-B-A-B", ref="SW4")
    sw.cn({1: "RUN_SW", 2: "GND"})
    c.R("220R", "RUN_PG", "RUN_SW", L["R220"], sh)
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          11: "I2C0_SCL", 12: "I2C0_SDA", 13: "GND", 14: "CM4_3V3", 15: "CM4_3V3", "MP": "GND"})
    j = c.add("J", "HomeDeck", "FPC_15P_1.0mm", "CAMERA (CAM1)", None, "C66660", sh, mpn="1.0-15PContact,Bottom", basic=False, ref="J7", desc="15-pin 1.0mm FPC, bottom contact, right angle (BOOMELE)")
    j.cn({1: "GND", 2: "CSI_D0_N", 3: "CSI_D0_P", 4: "GND", 5: "CSI_D1_N", 6: "CSI_D1_P", 7: "GND", 8: "CSI_C_N", 9: "CSI_C_P", 10: "GND",
          11: "CAM_GPIO", 13: "I2C0_SCL", 14: "I2C0_SDA", 15: "CM4_3V3", "MP": "GND"})
    j.nc.add("12")
    jj = c.add("J", "Connector_Generic", "Conn_01x03", "DISPLAY 5V", "Connector_PinHeader_2.54mm:PinHeader_1x03_P2.54mm_Vertical", "C124376", sh, mpn="B-2100S03P-A110", ref="J8")
    jj.cn({1: "5V_PERIPH", 2: "5V_PERIPH", 3: "GND"})
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    c.R("10k", "3V3", "SD_PWR_G", L["R10k"], sh)
    q = c.add("Q", "Transistor_FET", "2N7002", "2N7002", None, "C8545", sh, mpn="2N7002", basic=True, ref="Q2")
    q.c(G="SD_PWR_ON", D="SD_PWR_G", S="GND")
    c.R("10k", "CM4_3V3", "SD_PWR_ON", L["R10k"], sh)   # pull-up referenced to the CM4 rail like every other CM4 pin
    c.C("10uF", "SD_VDD", "GND", L["C10u_0603"], sh)
    c.C("100nF", "SD_VDD", "GND", L["C100n"], sh)

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
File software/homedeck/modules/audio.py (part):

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    subprocess.run(["pinctrl", "set", str(n), "op", "dh" if level else "dl"], capture_output=True, timeout=5)


# Pop-free power sequencing. Pins: GPIO4 = AMP_SDZ (amp enable, 10k pull-down: off at reset), GPIO5 = AMP_MUTE
# (high = muted), GPIO24 = DAC_XSMT (DAC soft-mute, low = muted, 10k pull-up). The pop came from switching the amp on
# unmuted while the DAC had no I2S clock (at boot) and from the amp losing its enable mid-signal (at reboot).
def _amp_always_on():
    """Boot: amp enabled but muted, DAC soft-muted, then start the I2S clocks with a second of silence and only
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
